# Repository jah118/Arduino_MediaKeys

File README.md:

# Arduino_MediaKeys

This project is to make custom key for windows, as of now it is used for media keys (prev,next,play/pause) and to use F19 and F16 to keybinds for discord or what key is defined

the future for project, is to add a display that can pull information from spotify and display the song and more info as a start.

# Dependencies:

HID-Project by NicoHood Version 2.5.0 or above

- can be found in Arduino Lirary Manager
- or: https://github.com/NicoHood/HID

BOUNCE 2 Debouncing library for Arduino and Wiring by Thomas Ouellet Fredericks
- can be found in Arduino Lirary Manager
- or:  https://github.com/thomasfredericks/Bounce2

# Reference:

The Reference links below is where the info to getting the project to work comes from

- https://uboopenfactory.univ-brest.fr/Les-Labs/MusicLab/Projets/Arduino-Media-Keys

## Most code inspiration comes from here:

- https://github.com/NicoHood/HID/wiki
- https://www.arduino.cc/reference/en/language/functions/usb/keyboard/
- https://www.stefanjones.ca/blog/arduino-leonardo-remote-multimedia-keys/
- https://arduino.stackexchange.com/questions/8934/send-keyboard-media-keys-with-keyboard-library
- http://www.freebsddiary.org/APC/usb_hid_usages.php
- list of hid codes for further use or differt use case
  https://www.instructables.com/id/USB-Volume-Control-and-Caps-Lock-LED-Simple-Cheap-/

# PCB

`the pcb was design in eagle`  

### With old prototype board

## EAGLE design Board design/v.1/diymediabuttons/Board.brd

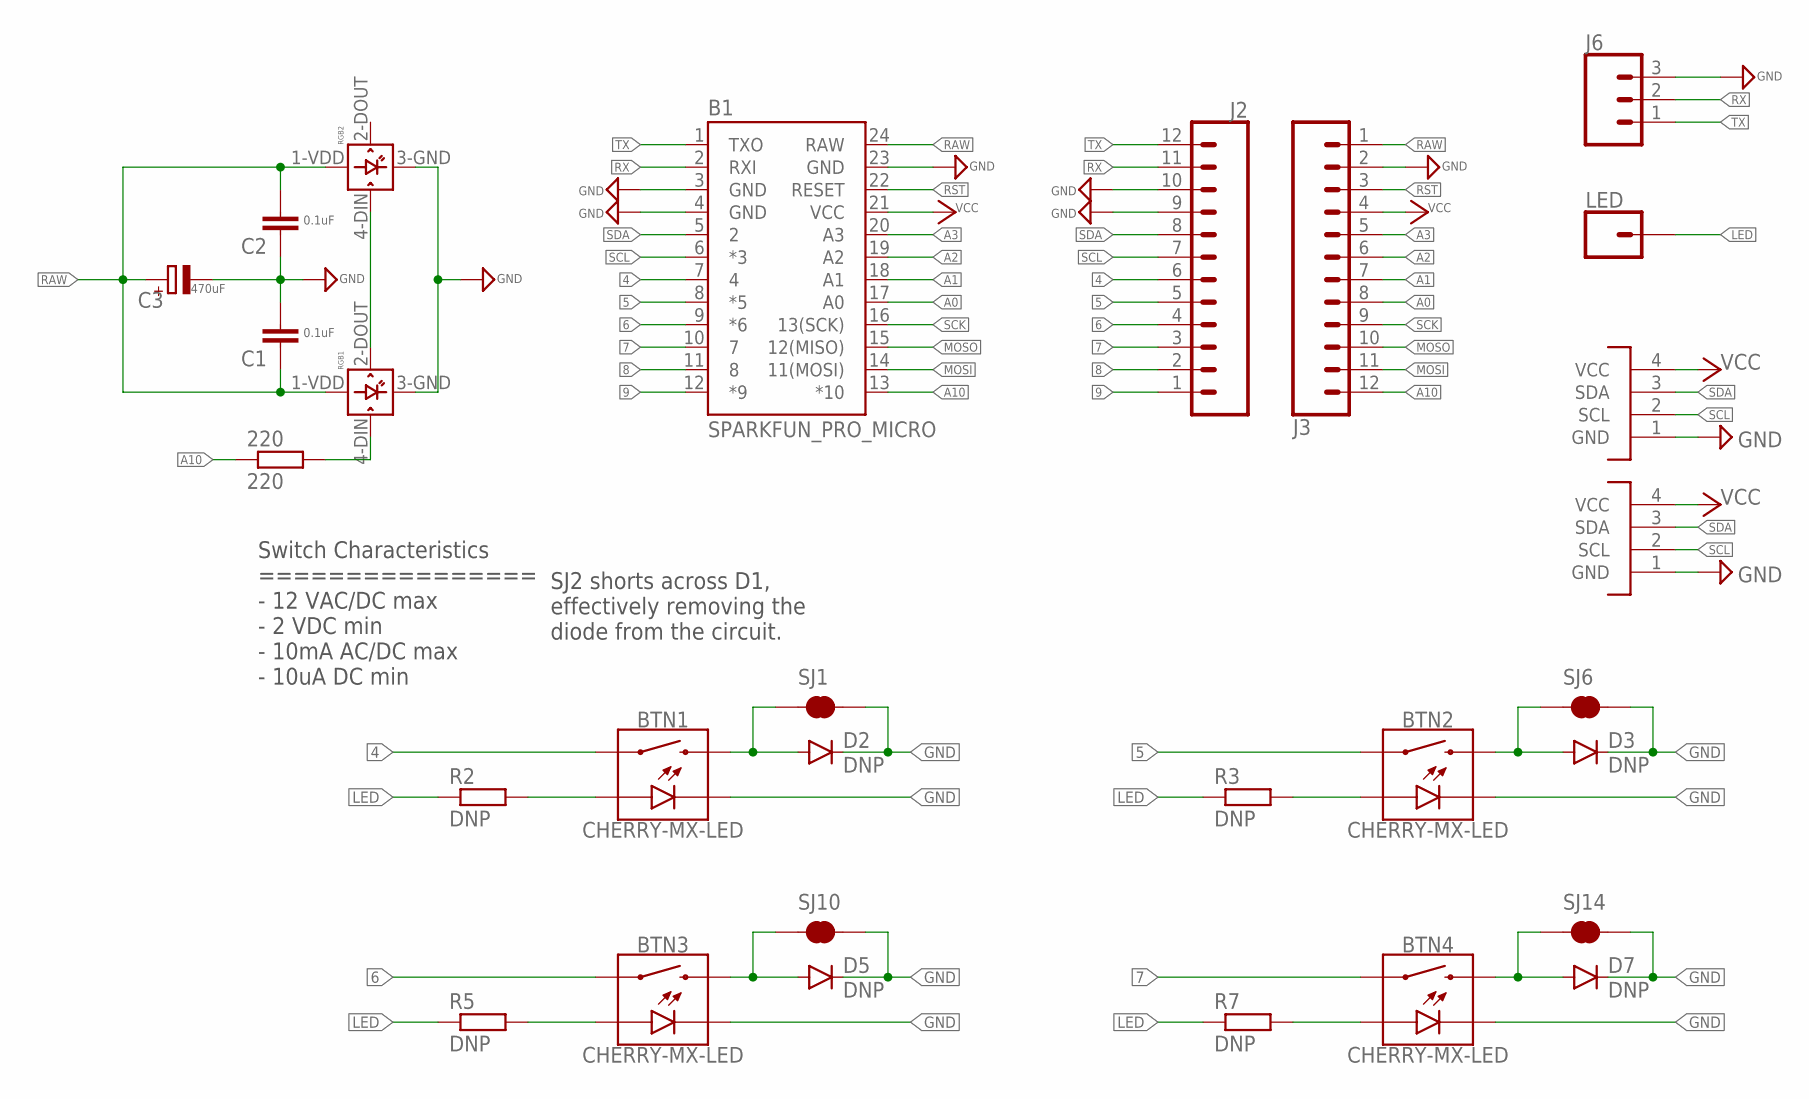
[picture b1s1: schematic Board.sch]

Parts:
220: 220; 0207/10
B1: SPARKFUN_PRO_MICRO
BTN1, BTN2, BTN3, BTN4: CHERRY-MX-LED
C1, C2: 0.1uF; CAP-PTH-SMALL-KIT
C3: 470uF; E3,5-8
D2, D3, D5, D7: DNP; DIODE-PTH-0.1
J2, J3: CONN_12; 1X12
J4, J5: I2C-HEADER; HEADER-4X1-2.54
J6: CONN_03; 1X03
LED: CONN_01; 1X01
R2, R3, R5, R7: DNP; 0207/10
RGB1, RGB2: WS2812B
SJ1, SJ6, SJ10, SJ14: JUMPER-PAD-2-NC_BY_TRACENO_SILK; PAD-JUMPER-2-NC_BY_TRACE_NO_SILK

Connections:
4: B1.7 (4), BTN1.S1, J2.6
5: B1.8 (*5), BTN2.S1, J2.5
6: B1.9 (*6), BTN3.S1, J2.4
7: B1.10 (7), BTN4.S1, J2.3
8: B1.11 (8), J2.2
9: B1.12 (*9), J2.1
A0: B1.17 (A0), J3.8
A1: B1.18 (A1), J3.7
A2: B1.19 (A2), J3.6
A3: B1.20 (A3), J3.5
A10: 220.1, B1.13 (*10), J3.12
GND: B1.3 (GND), B1.4 (GND), B1.23 (GND), BTN1.K (C), BTN2.K (C), BTN3.K (C), BTN4.K (C), C1.2, C2.1, C3.-, D2.C, D3.C, D5.C, D7.C, J2.9, J2.10, J3.2, J4.1 (GND), J5.1 (GND), J6.3, RGB1.3-GND (GND), RGB2.3-GND (GND), SJ1.2, SJ6.2, SJ10.2, SJ14.2
LED: LED.1, R2.1, R3.1, R5.1, R7.1
MOSI: B1.14 (11(MOSI)), J3.11
MOSO: B1.15 (12(MISO)), J3.10
unnamed: BTN1.A, R2.2
unnamed: 220.2, RGB1.4-DIN (DIN)
unnamed: RGB1.2-DOUT (DOUT), RGB2.4-DIN (DIN)
unnamed: BTN1.S2, D2.A, SJ1.1
unnamed: BTN2.A, R3.2
unnamed: BTN2.S2, D3.A, SJ6.1
unnamed: BTN3.A, R5.2
unnamed: BTN3.S2, D5.A, SJ10.1
unnamed: BTN4.A, R7.2
unnamed: BTN4.S2, D7.A, SJ14.1
RAW: B1.24 (RAW), C1.1, C2.2, C3.+, J3.1, RGB1.1-VDD (VDD), RGB2.1-VDD (VDD)
RST: B1.22 (RESET), J3.3
RX: B1.2 (RXI), J2.11, J6.2
SCK: B1.16 (13(SCK)), J3.9
SCL: B1.6 (*3), J2.7, J4.2 (SCL), J5.2 (SCL)
SDA: B1.5 (2), J2.8, J4.3 (SDA), J5.3 (SDA)
TX: B1.1 (TXO), J2.12, J6.1
VCC: B1.21 (VCC), J3.4, J4.4 (VCC), J5.4 (VCC)

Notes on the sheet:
SJ2 shorts across D1, effectively removing the diode from the circuit.
Switch Characteristics ================ - 12 VAC/DC max - 2 VDC min - 10mA AC/DC max - 10uA DC min

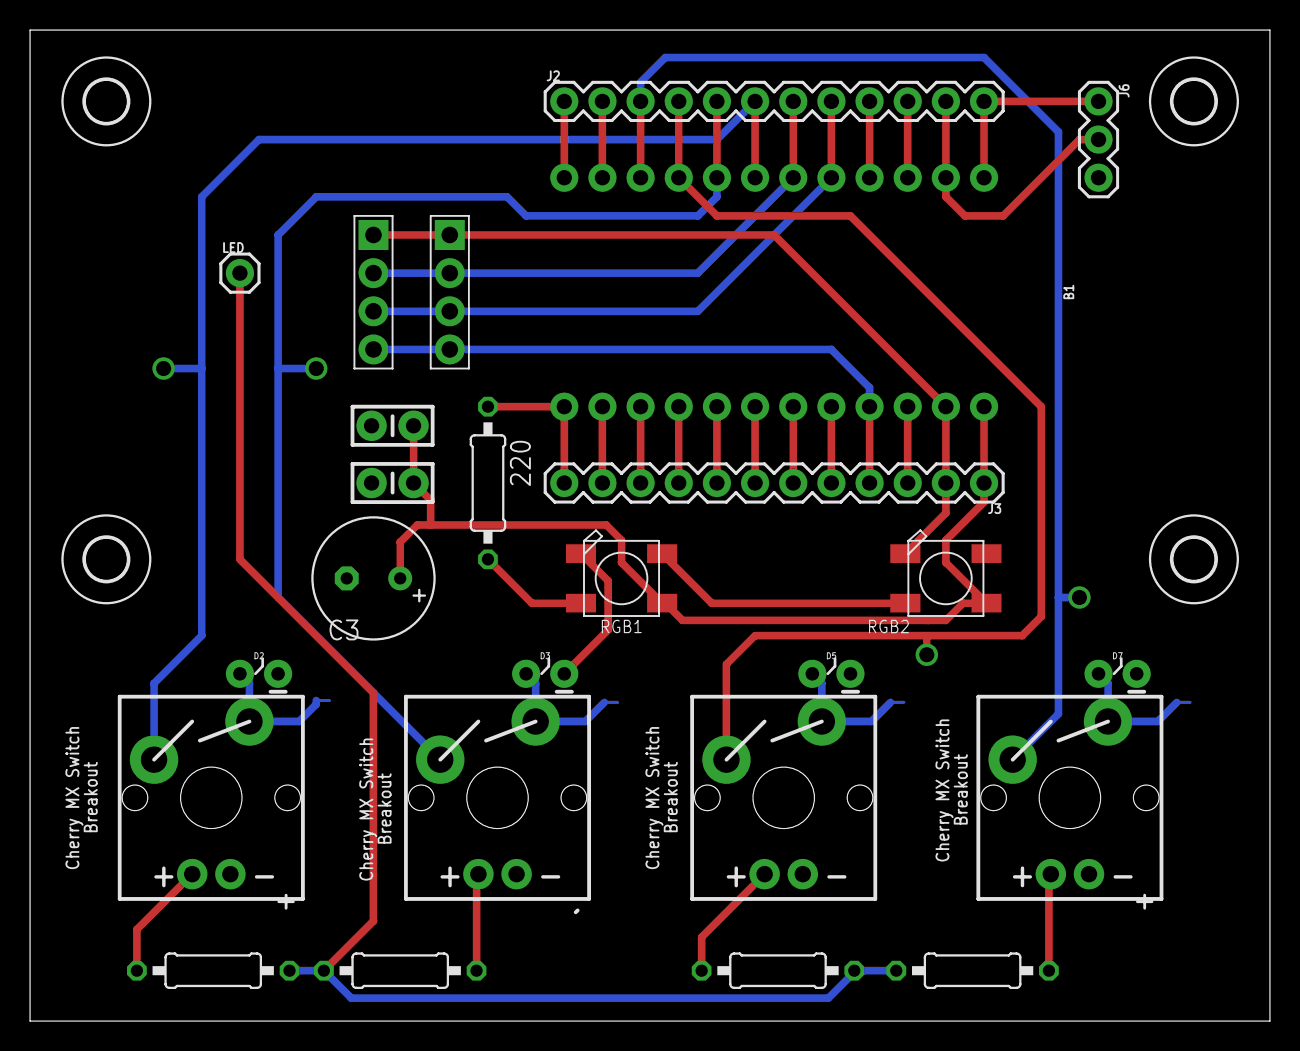
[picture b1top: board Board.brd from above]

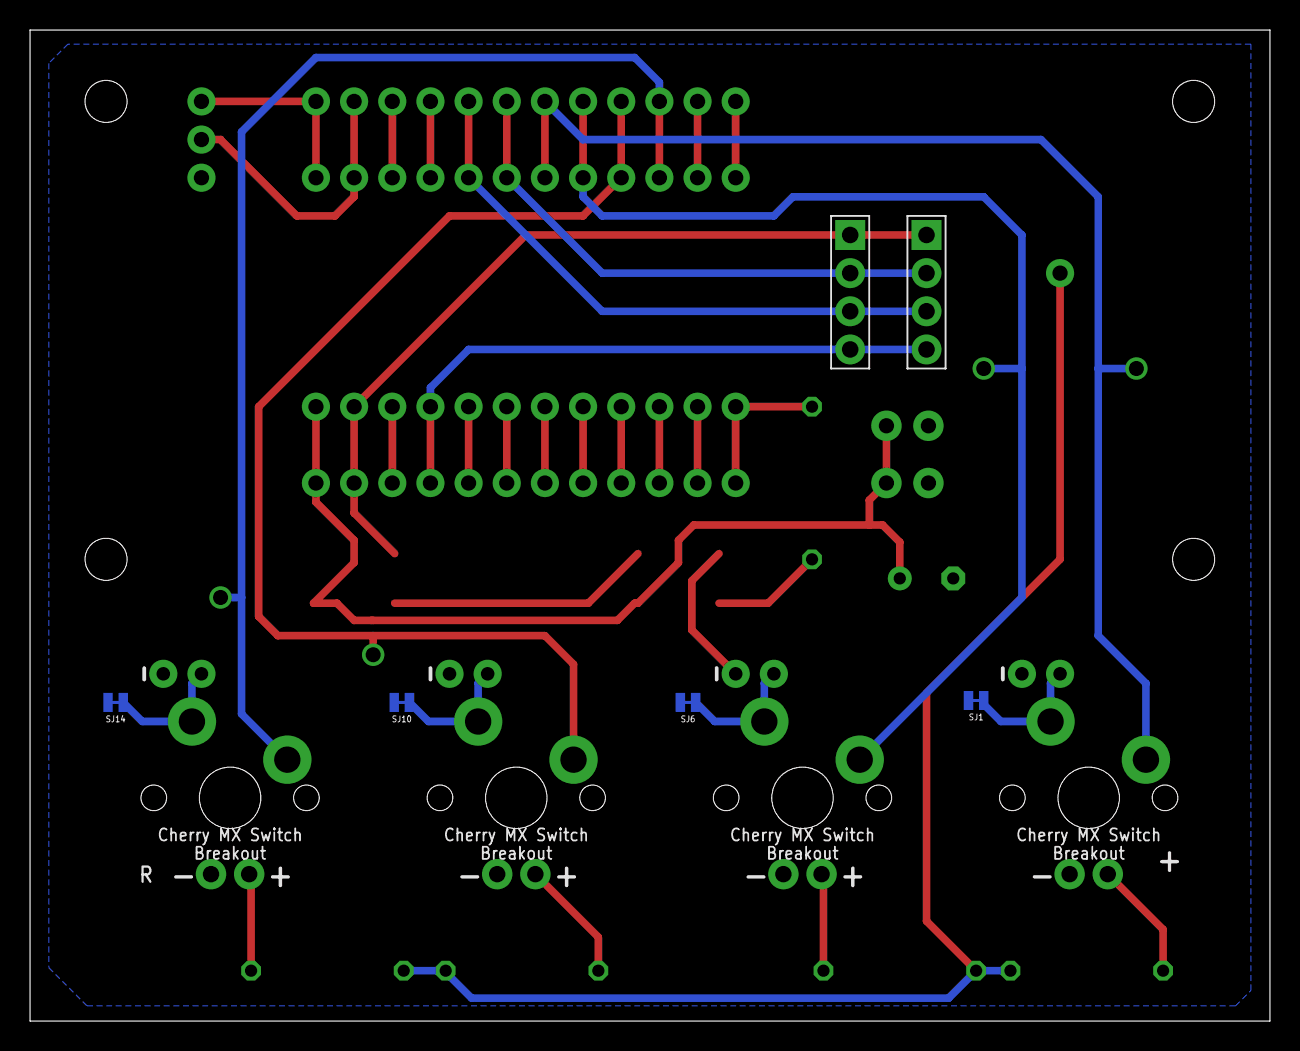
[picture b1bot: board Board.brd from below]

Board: 2 copper layers, 82.5 x 66.0 mm, 33 parts (4 on the bottom side), 33 nets.

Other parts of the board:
U$1, U$2, U$3, U$4: 2,8

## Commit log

2020-09-03 change of folder
2020-10-04 changed dir
2020-10-04 new begining
2020-10-04 hide ids
2020-10-05 cleanup
2020-10-12 removed magik nubers
2020-10-12 Update mediaKEYS__works.ino
    Removed dead code
2020-10-12 dead code removed
2020-10-14 switch to turnOnRGBByState funktion
    turnOnRGBByState is used now instead of having dulicet code and removede dead code where state is check for within a state for single press and removed debug prints
2020-10-14 Update mediaKEYS__works.ino
    dead code removed
    added comments
2020-10-24 updated nuget
2021-02-25 Update mediaKEYS_Single_Double_Pres.ino
    changed key
2021-03-22 added pcb board
2021-03-22 added pictures
2021-04-02 Changed from boot keyboard to improved
    - clean up code with a loop
    - added refernce
    - reformated code
2022-02-06 Clean up and prep for V2
2022-02-06 Create mediaKEYS__works_2.ino
    Made version 2 based on bounce2 for more stabel presses
2022-02-07 Cleanup and renames
2022-02-07 more clean up
2022-02-11 Updated goal for code
2022-02-15 split out to libs
2022-02-22 exsample for how button data could be saved
2022-02-22 first issue
2022-02-22 add logic that marches json
2022-02-27 Button lib works. config lib started
    the commit fokus on getting button func done and some trail and error about loading things to eeprom
2022-03-06 refactoring
2022-06-23 Bump Newtonsoft.Json
    Bumps [Newtonsoft.Json](https://github.com/JamesNK/Newtonsoft.Json) from 12.0.3 to 13.0.1.
    - [Release notes](https://github.com/JamesNK/Newtonsoft.Json/releases)
    - [Commits](https://github.com/JamesNK/Newtonsoft.Json/compare/12.0.3...13.0.1)
    ---
    updated-dependencies:
    - dependency-name: Newtonsoft.Json
2022-06-23 Bump Newtonsoft.Json
    Bumps [Newtonsoft.Json](https://github.com/JamesNK/Newtonsoft.Json) from 12.0.2 to 13.0.1.
    - [Release notes](https://github.com/JamesNK/Newtonsoft.Json/releases)
    - [Commits](https://github.com/JamesNK/Newtonsoft.Json/compare/12.0.2...13.0.1)
    ---
    updated-dependencies:
    - dependency-name: Newtonsoft.Json
2022-12-08 Bump Newtonsoft.Json
    Bumps [Newtonsoft.Json](https://github.com/JamesNK/Newtonsoft.Json) from 12.0.2 to 13.0.2.
    - [Release notes](https://github.com/JamesNK/Newtonsoft.Json/releases)
    - [Commits](https://github.com/JamesNK/Newtonsoft.Json/compare/12.0.2...13.0.2)
    ---
    updated-dependencies:
    - dependency-name: Newtonsoft.Json
2022-12-08 Bump Newtonsoft.Json
    Bumps [Newtonsoft.Json](https://github.com/JamesNK/Newtonsoft.Json) from 12.0.3 to 13.0.2.
    - [Release notes](https://github.com/JamesNK/Newtonsoft.Json/releases)
    - [Commits](https://github.com/JamesNK/Newtonsoft.Json/compare/12.0.3...13.0.2)
    ---
    updated-dependencies:
    - dependency-name: Newtonsoft.Json
2023-02-18 Bump Newtonsoft.Json in /src/Program_COde/SpotifyApiToSerial/spotifyApi
    Bumps [Newtonsoft.Json](https://github.com/JamesNK/Newtonsoft.Json) from 12.0.3 to 13.0.1.
    - [Release notes](https://github.com/JamesNK/Newtonsoft.Json/releases)
    - [Commits](https://github.com/JamesNK/Newtonsoft.Json/compare/12.0.3...13.0.1)
    ---
    updated-dependencies:
    - dependency-name: Newtonsoft.Json
2023-12-10 Be gone Dead code
2023-12-10 Update: Format file
2023-12-10 Refactor: Removed line
2023-12-10 Update: ctor change
2023-12-10 Update: press(), handleButton4Press(), cleaning
    * press() - added diff time hanfle for press checks
    * handleButton4Press() - moved logic to func and redid hold check
2023-12-10 Update 3_media_keys_1_custom_key.ino
    Temp commit as fall back to lazy to branch
2023-12-10 Update: New doubleClickEvent works
2023-12-10 Refacor: Removed comments and dead code
    last commit for new release
2023-12-10 Update: turnOnRGBByState, base variables
2023-12-17 Refactor: Changed comment style
    - Updated: pressEventHandler to take KeyboardKeycode to make use of buttonPin4Action1 and buttonPin4Action2
    - The code now uses /// instead of //, for general comments

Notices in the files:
parts and their libraries:
SparkFun-Boards: Licensing: Creative Commons ShareAlike 4.0 International - https://creativecommons.org/licenses/by-sa/4.0
